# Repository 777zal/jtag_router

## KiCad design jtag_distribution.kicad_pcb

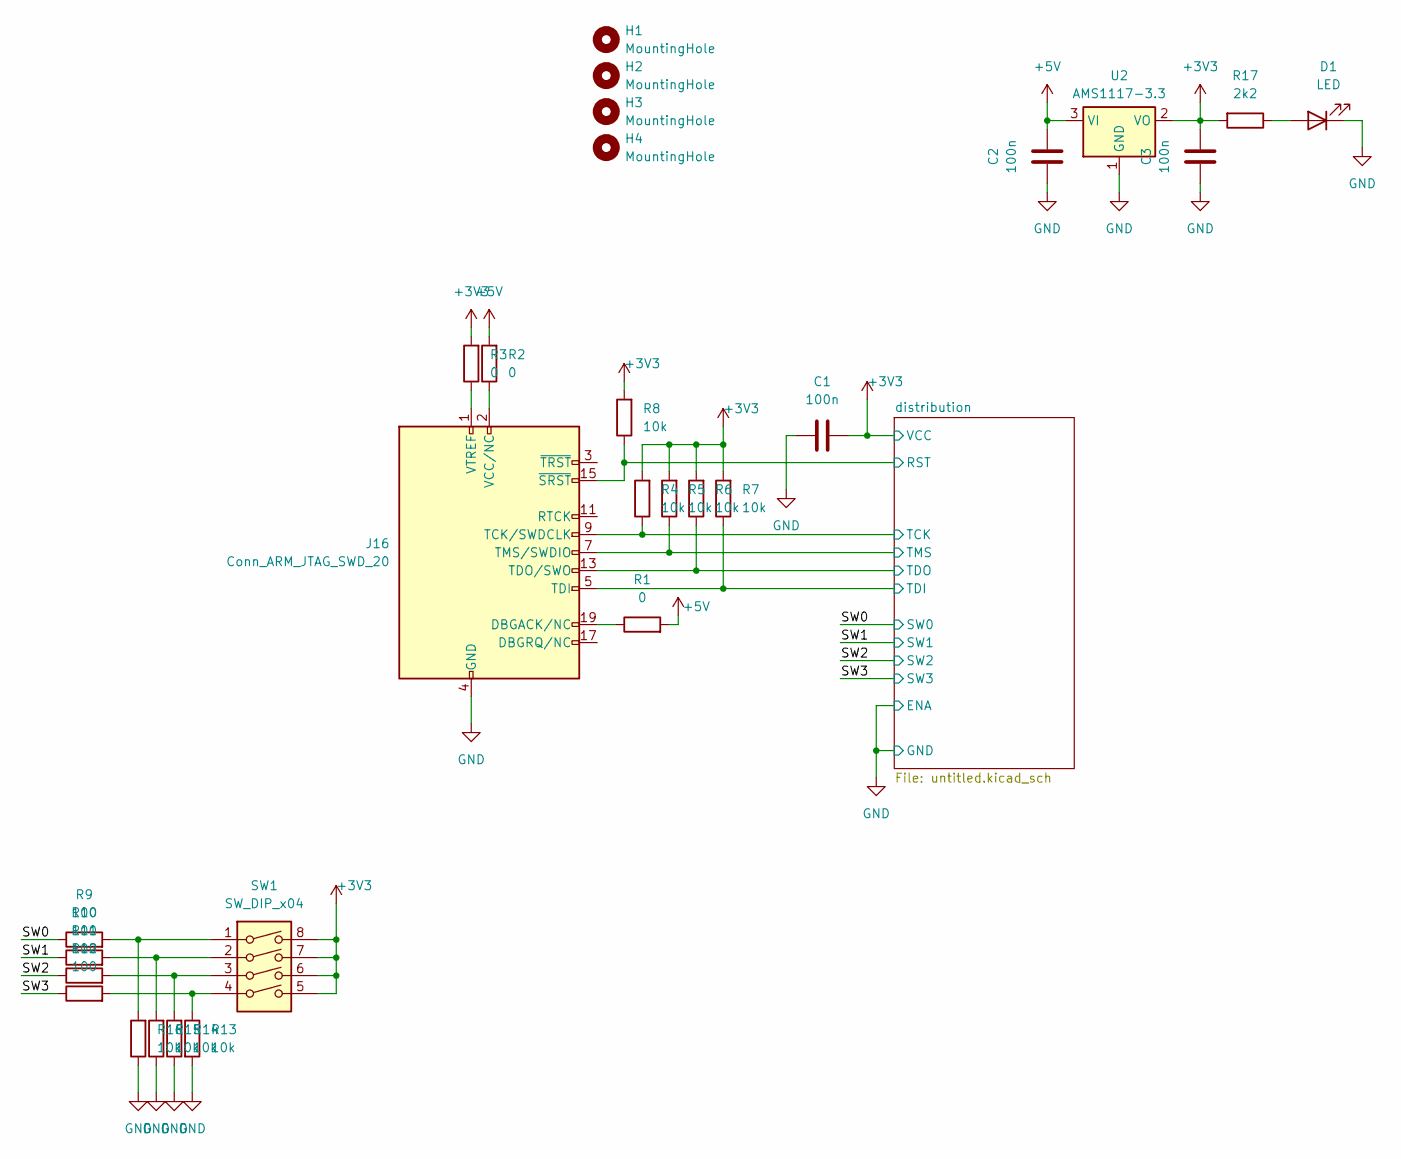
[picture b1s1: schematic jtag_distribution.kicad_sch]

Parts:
C1, C2, C3: 100n; C_0805_2012Metric
D1: LED; LED_0805_2012Metric
H1, H2, H3, H4: MountingHole; MountingHole_3mm
J16: Conn_ARM_JTAG_SWD_20; IDC-Header_2x10_P2.54mm_Vertical
R1, R2, R3: 0; R_0805_2012Metric
R4, R5, R6, R7, R8, R13, R14, R15, R16: 10k; R_0805_2012Metric
R9, R10, R11, R12: 100; R_0805_2012Metric
R17: 2k2; R_0805_2012Metric
SW1: SW_DIP_x04; SW_DIP_SPSTx04_Slide_6.7x11.72mm_W7.62mm_P2.54mm_LowProfile
U2: AMS1117-3.3; SOT-223-3_TabPin2

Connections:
+3V3: C1.2, C3.2, R3.2, R4.2, R5.2, R6.2, R7.2, R8.2, R17.2, SW1.5, SW1.6, SW1.7, SW1.8, U2.2 (VO); also elsewhere on the board
+5V: C2.2, R1.2, R2.2, U2.3 (VI)
/SW0: R9.1; also elsewhere on the board
/SW1: R10.1; also elsewhere on the board
/SW2: R11.1; also elsewhere on the board
/SW3: R12.1; also elsewhere on the board
/distribution/RST: J16.15 (~SRST), R8.1; also elsewhere on the board
/distribution/TCK: J16.9 (TCK/SWDCLK), R4.1; also elsewhere on the board
/distribution/TDI: J16.5 (TDI), R7.1; also elsewhere on the board
/distribution/TDO: J16.13 (TDO/SWO), R6.1; also elsewhere on the board
/distribution/TMS: J16.7 (TMS/SWDIO), R5.1; also elsewhere on the board
GND: C1.1, C2.1, C3.1, D1.1 (K), J16.4 (GND), J16.6 (GND), J16.8 (GND), J16.10 (GND), J16.12 (GND), J16.14 (GND), J16.16 (GND), J16.18 (GND), J16.20 (GND), R13.2, R14.1, R15.1, R16.1, U2.1 (GND); also elsewhere on the board
unnamed: D1.2 (A), R17.1
unnamed: J16.19 (DBGACK/NC), R1.1
unnamed: J16.2 (VCC/NC), R2.1
unnamed: J16.1 (VTREF), R3.1
unnamed: R10.2, R15.2, SW1.2
unnamed: R11.2, R14.2, SW1.3
unnamed: R12.2, R13.1, SW1.4
unnamed: R9.2, R16.2, SW1.1

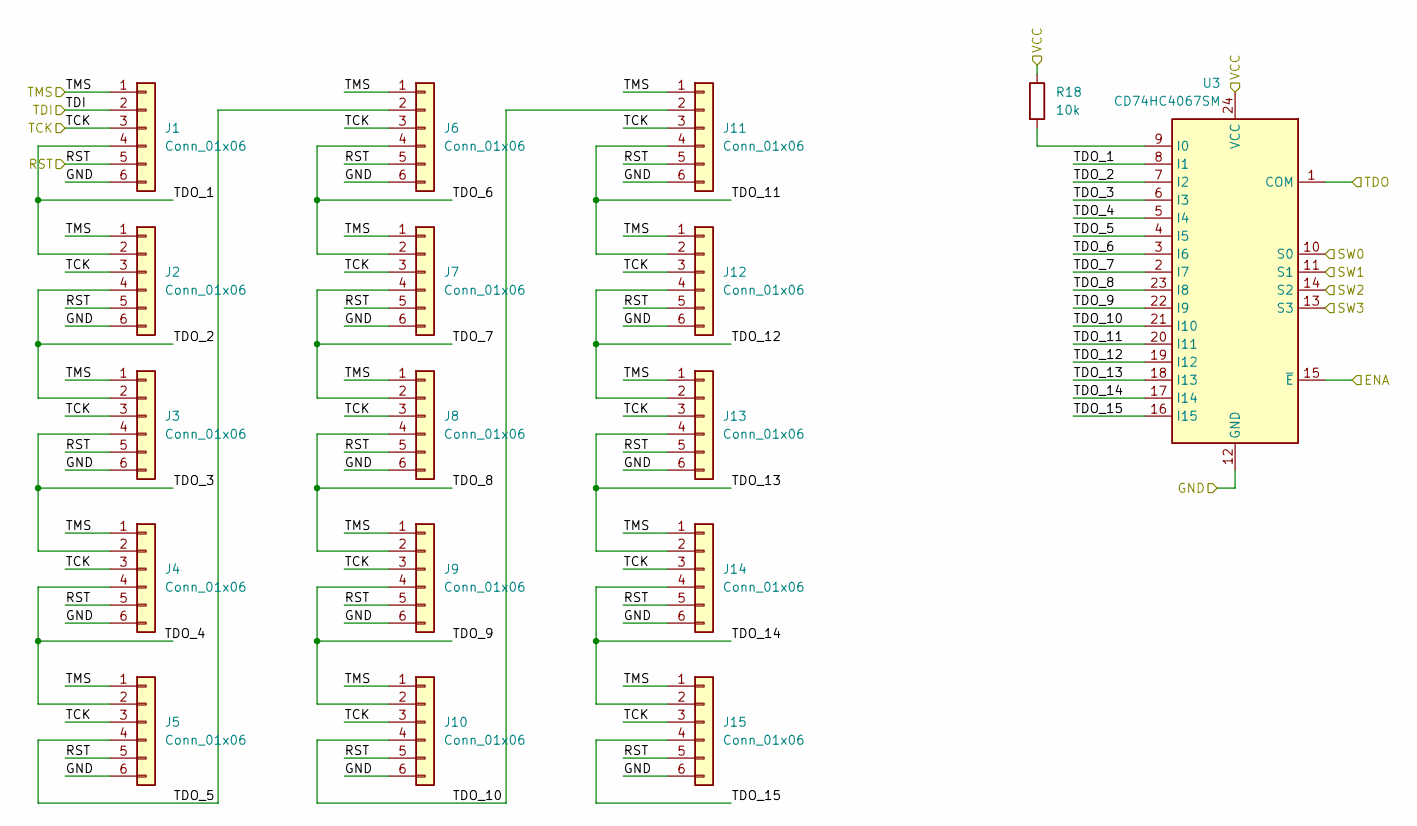
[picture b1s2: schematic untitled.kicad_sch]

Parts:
J1, J2, J3, J4, J5, J6, J7, J8, J9, J10, J11, J12, J13, J14, J15: Conn_01x06; IDC-Header_2x03_P2.54mm_Vertical
R18: 10k; R_0805_2012Metric
U3: CD74HC4067SM; SSOP-24_5.3x8.2mm_P0.65mm

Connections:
+3V3: R18.1, U3.24 (VCC); also elsewhere on the board
/SW0: U3.10 (S0); also elsewhere on the board
/SW1: U3.11 (S1); also elsewhere on the board
/SW2: U3.14 (S2); also elsewhere on the board
/SW3: U3.13 (S3); also elsewhere on the board
/distribution/RST: J1.5, J2.5, J3.5, J4.5, J5.5, J6.5, J7.5, J8.5, J9.5, J10.5, J11.5, J12.5, J13.5, J14.5, J15.5; also elsewhere on the board
/distribution/TCK: J1.3, J2.3, J3.3, J4.3, J5.3, J6.3, J7.3, J8.3, J9.3, J10.3, J11.3, J12.3, J13.3, J14.3, J15.3; also elsewhere on the board
/distribution/TDI: J1.2; also elsewhere on the board
/distribution/TDO: U3.1 (COM); also elsewhere on the board
/distribution/TDO_1: J1.4, J2.2, U3.8 (I1)
/distribution/TDO_2: J2.4, J3.2, U3.7 (I2)
/distribution/TDO_3: J3.4, J4.2, U3.6 (I3)
/distribution/TDO_4: J4.4, J5.2, U3.5 (I4)
/distribution/TDO_5: J5.4, J6.2, U3.4 (I5)
/distribution/TDO_6: J6.4, J7.2, U3.3 (I6)
/distribution/TDO_7: J7.4, J8.2, U3.2 (I7)
/distribution/TDO_8: J8.4, J9.2, U3.23 (I8)
/distribution/TDO_9: J9.4, J10.2, U3.22 (I9)
/distribution/TDO_10: J10.4, J11.2, U3.21 (I10)
/distribution/TDO_11: J11.4, J12.2, U3.20 (I11)
/distribution/TDO_12: J12.4, J13.2, U3.19 (I12)
/distribution/TDO_13: J13.4, J14.2, U3.18 (I13)
/distribution/TDO_14: J14.4, J15.2, U3.17 (I14)
/distribution/TDO_15: J15.4, U3.16 (I15)
/distribution/TMS: J1.1, J2.1, J3.1, J4.1, J5.1, J6.1, J7.1, J8.1, J9.1, J10.1, J11.1, J12.1, J13.1, J14.1, J15.1; also elsewhere on the board
GND: J1.6, J2.6, J3.6, J4.6, J5.6, J6.6, J7.6, J8.6, J9.6, J10.6, J11.6, J12.6, J13.6, J14.6, J15.6, U3.12 (GND), U3.15 (~E); also elsewhere on the board
unnamed: R18.2, U3.9 (I0)

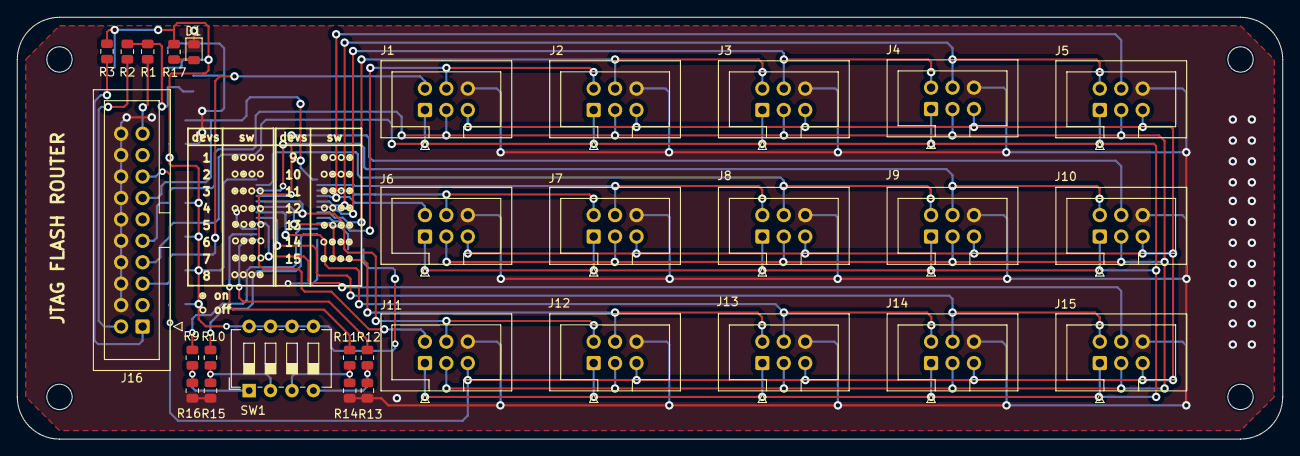
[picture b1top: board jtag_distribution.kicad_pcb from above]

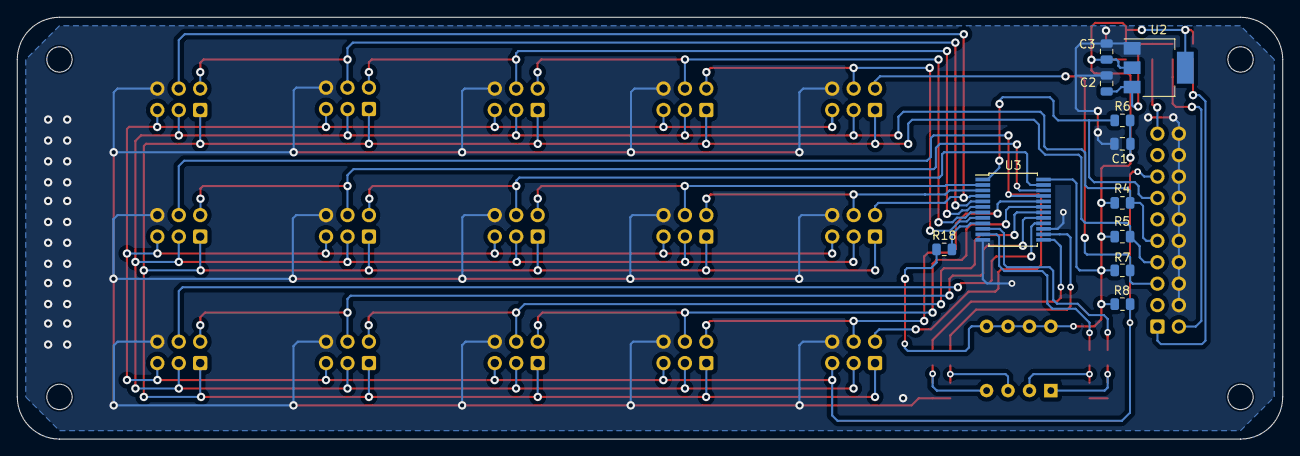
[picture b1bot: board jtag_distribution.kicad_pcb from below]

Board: 2 copper layers, 150.0 x 50.0 mm, 45 parts (11 on the bottom side), 36 nets.

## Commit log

2024-10-17 change dip switch type, change reset position
